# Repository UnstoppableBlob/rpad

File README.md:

# RPad

A 9-key macropad with macros for quickly typing email, etc.; media controls; window controls. Also has a very important alt+f4 key. It has 2 rotary encoders that are supposed to set volume and brightness and a OLED that should display that info and the time.

### BOM
- 9x MX Switches
- 9x Blank DSA keycaps
- 1x 0.91" OLED
- 2x EC11 Rotary Encoder
- 1x IO Expander
- 1x XIAO
- 2x resistors 4.7kOhm
- 4x M3x16mm screws
- 4x M3x5mx4mm heatset inserts

### Schematic and PCB (KiCad)

### 3D Model (Shapr3D)

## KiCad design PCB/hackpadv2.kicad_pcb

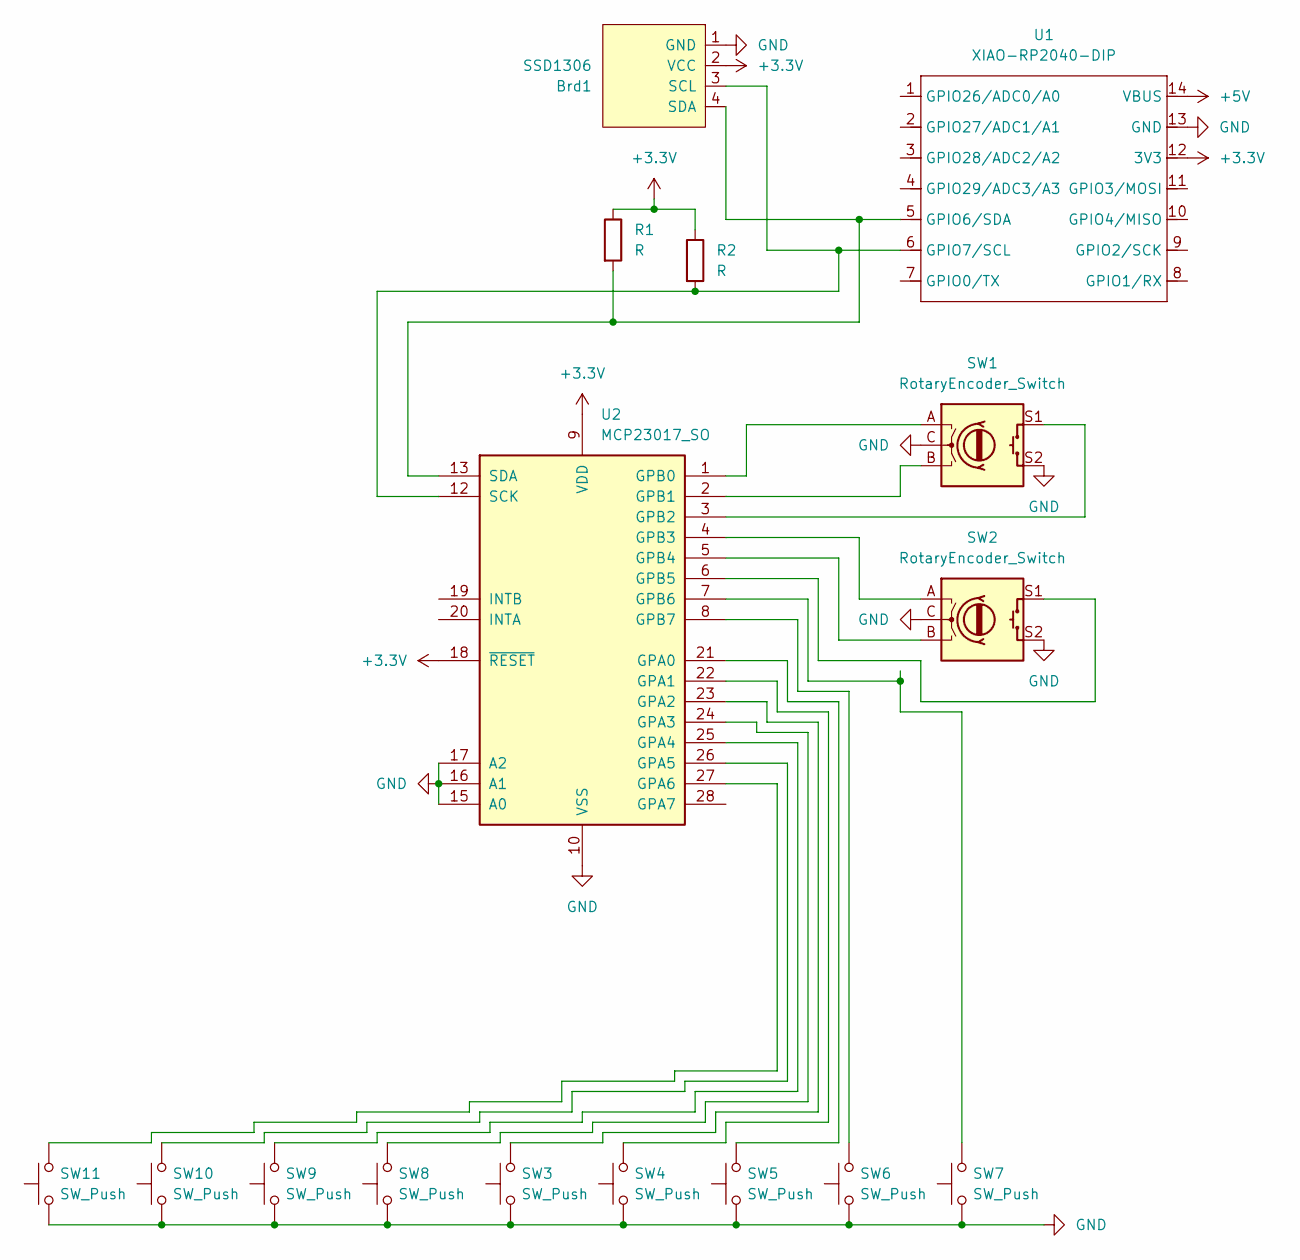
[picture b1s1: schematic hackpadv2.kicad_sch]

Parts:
Brd1: SSD1306; PinHeader_1x04_P2.54mm_Horizontal
R1, R2: R; R_Axial_DIN0204_L3.6mm_D1.6mm_P7.62mm_Horizontal
SW1, SW2: RotaryEncoder_Switch; RotaryEncoder_Alps_EC11E-Switch_Vertical_H20mm_CircularMoun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
SW3, SW4, SW5, SW6, SW7, SW8, SW9, SW10, SW11: SW_Push; SW_Cherry_MX_1.00u_PCB
U1: XIAO-RP2040-DIP
U2: MCP23017_SO; SOIC-28W_7.5x17.9mm_P1.27mm

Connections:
+3.3V: Brd1.2 (VCC), R1.1, R2.1, U1.12 (3V3), U2.9 (VDD), U2.18 (~RESET)
+5V: U1.14 (VBUS)
GND: Brd1.1 (GND), SW1.C, SW1.S2, SW2.C, SW2.S2, SW3.1, SW4.1, SW5.1, SW6.1, SW7.1, SW8.1, SW9.1, SW10.1, SW11.1, U1.13 (GND), U2.10 (VSS), U2.15 (A0), U2.16 (A1), U2.17 (A2)
unnamed: Brd1.3 (SCL), R2.2, U1.6 (GPIO7/SCL), U2.12 (SCK)
unnamed: Brd1.4 (SDA), R1.2, U1.5 (GPIO6/SDA), U2.13 (SDA)
unnamed: SW5.2, U2.21 (GPA0)
unnamed: SW4.2, U2.22 (GPA1)
unnamed: SW3.2, U2.23 (GPA2)
unnamed: SW8.2, U2.24 (GPA3)
unnamed: SW9.2, U2.25 (GPA4)
unnamed: SW10.2, U2.26 (GPA5)
unnamed: SW11.2, U2.27 (GPA6)
unnamed: SW1.A, U2.1 (GPB0)
unnamed: SW1.B, U2.2 (GPB1)
unnamed: SW1.S1, U2.3 (GPB2)
unnamed: SW2.A, U2.4 (GPB3)
unnamed: SW2.B, U2.5 (GPB4)
unnamed: SW2.S1, U2.6 (GPB5)
unnamed: SW7.2, U2.7 (GPB6)
unnamed: SW6.2, U2.8 (GPB7)

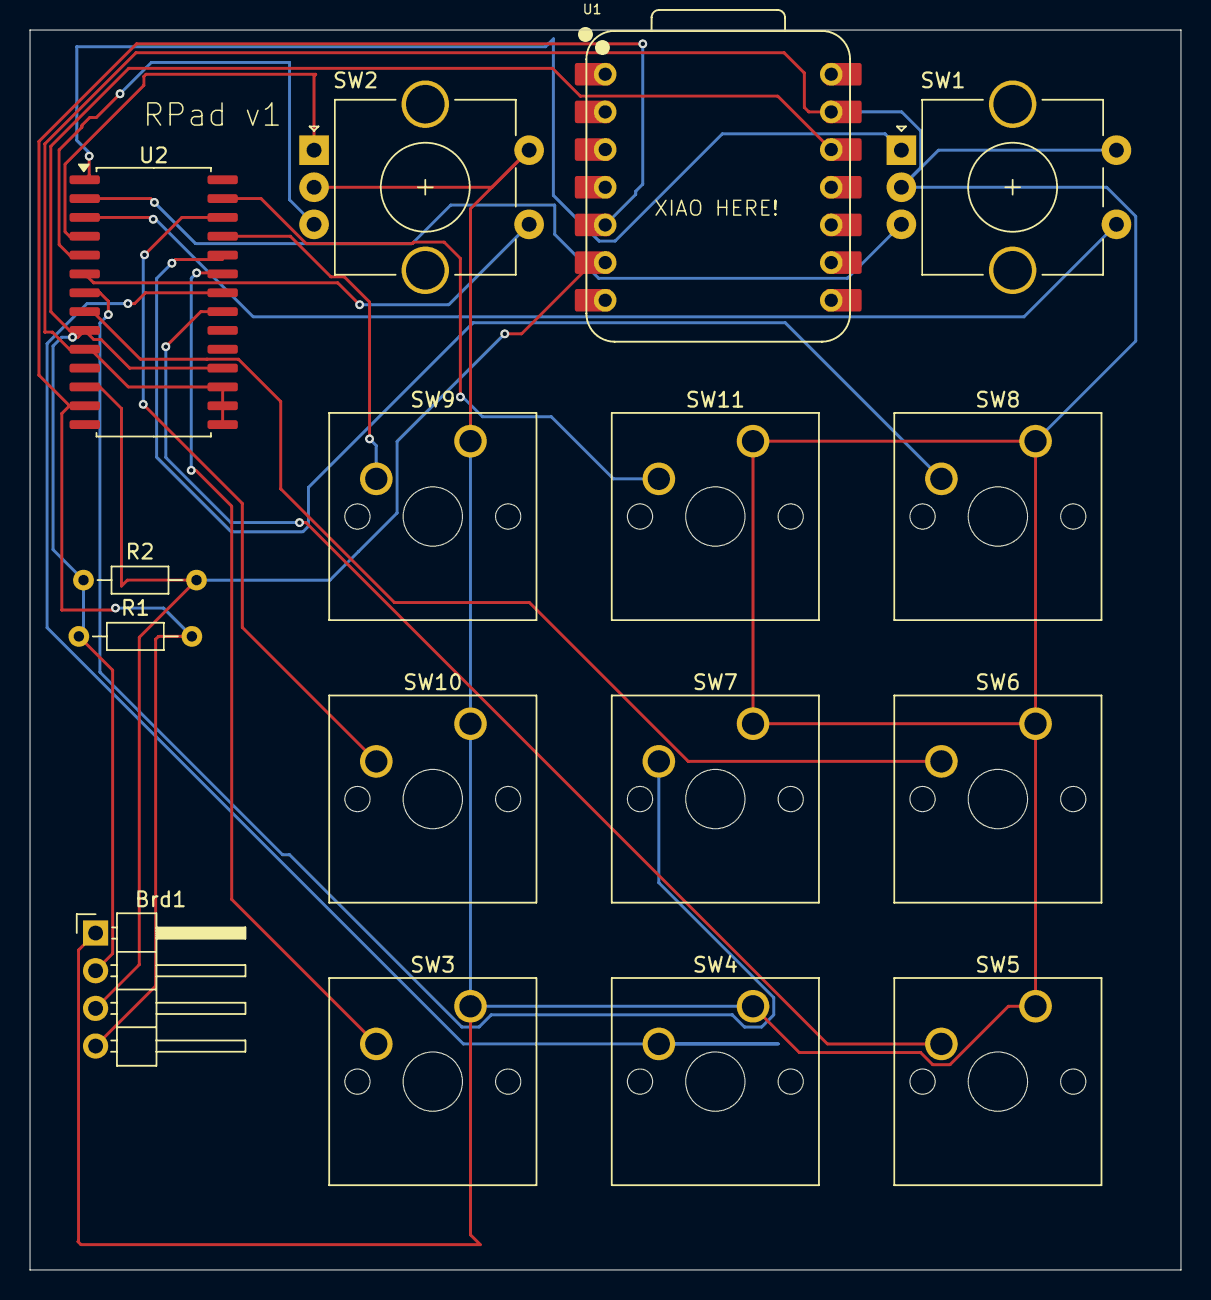
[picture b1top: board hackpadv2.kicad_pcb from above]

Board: 2 copper layers, 77.6 x 83.6 mm, 16 parts (0 on the bottom side), 19 nets.

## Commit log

2025-07-30 save
